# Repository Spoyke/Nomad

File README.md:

# **Son Spatial**
*Projet étudiant S7*

## Description du projet 

Ce projet a pour objectif de créer un système audio immersif mobile grâce à un réseau d’amplificateurs audio, capables de spatialiser le son. Le principe repose sur la distribution et le traitement différencié des signaux audio entre plusieurs amplificateurs, afin de recréer une expérience sonore 3D pour l’utilisateur. Le système s'adapte aux différentes pièces pour trouver 

### Principe de fonctionnement 

#### Microcontrôleur maître

- Reçoit le contenu audio à diffuser (ex : musique, film, jeu vidéo).
- Traite et décompose le signal audio pour chaque ampli, en fonction de leur position relative par rapport à l’utilisateur.
- Envoie les données audio adaptées à chaque ampli via un protocole de communication sans fil.

#### Amplificateurs audio

- Reçoivent les signaux audio spécifiques (ex du stéréo : piste gauche pour l’ampli gauche, piste droite pour l’ampli droit).
- Convertissent le signal numérique en signal analogique, l’amplifient, et le diffusent via des haut-parleurs.
- Synchronisent leur diffusion pour éviter les décalages.

### Exemple

Si un son provient de la gauche dans le contenu audio, l’utilisateur l’entendra principalement depuis l’ampli situé à sa gauche, avec une atténuation progressive vers la droite. Plus le nombre d’amplis est élevé (ex : 4 ou 6), plus la précision de la spatialisation est fine (avant/arrière, haut/bas).

## Architecture du projet

Le projet est divisé en deux parties principales, chacune avec des objectifs techniques spécifiques :

### Partie électronique

Cette partie correspond à la concéption et à la réalisation des amplificateurs audio.

#### Fonctions clés 

- Récupération du signal audio numérique
- Conversion numérique → analogique
- Amplification du signal

### Partie Informatique

Cette partie comporte la programmation des microcontroleurs (esp32), Rasberry PI, application mobile.
On vise à traiter le son et assurer une communication synchrone entre le microcontrôleur maître et les amplis.
- Le traitement de signal sera géré par la Rasberry Pi commandé via une interface mobile. 
- La communication entre l'application du telephone et la raspberry pi se fera via un serveur local WebSocket hebergé par la raspberry.
- La diffusion de la musique entre la raspberry pi et l'esp32 se fera à travers un serveur local Icecast hebergé par la raspberry.

### Partie mécanique

Cette partie vise à conceptionner plusieurs robots capables de se déplacer dans une pièce. 

#### Fonctions clés

- Extraction des pistes (gauche/droite, avant/arrière)
- Synchronisation des amplis

## Compte rendus de séance
### Séance 1 (16/09/2025)

*Julie, Simon, Gabriel* :

Réalisation en amont des schématique :
- Amplificateur audio pour diffuser du son via une application mobile
- Mécanique pour déplacer l'enceinte et éviter les obstacles
  
Mettre en commun les schématique afin de commander les composantes. 

*Axel, Aleksandar* : 

Etablir une communication entre les esp32 - Rasberry Pi - Téléphone
Transmission de son via une application mobile

### Séance 2 (23/09/2025)

"Julie, Simon, Gabriel" : 

- Fin de la réalisation et mise en commun des schémas de l'ampli audio et du robot.
- Ajout d'un capteur à ultrason au robot pour qu'il puisse détecter et anticiper les obstacles. Utilisation du HC-SR04.
- Choix final de l'esp32 et des empreintes des composants pour le PCB. 
- Début de la conception du PCB.

"Axel, Aleks" :

Design de l'interface de l'application
Début de communication entre un esp32 et la raspberry Pi

"Globale" :
- Recherche sur la façon dont les robots se localiser et comment l'implémenter : On utilisera l'intensité du signal émit par la raspberry pi à l'esp32 pour déterminer la distance entre les deux (plus l'intensité est faible, plus la distance est grande)

Planning prévisionnel :

### Séance 3 (30/09/2025)

Simon : commande des composants, continuer le PCB

Gabriel : Finition placement des composants pour le routage, routage des composants sauf pour l'esp32. 

Aleksandar : ecrire un code pour teste l'intensité d'un signal wifi avec un appareil. On remarque que des interférences viennent rapidement perturber le signal. Il faudrait amplifier le signal wifi ou trouver un autre solution pour le localisation des robots.

Axel : transmission d'un fichier audio avec la rasberry Pi sur l'esp32. Vérifier que le signal est bien lu sur l'esp32 avec un oscilloscope. Le son n'est pas assez puissant pour pouvoir l'écouter.Implémentation d'un système d'amplification du courant à la prochaine séance via le dac de l'esp32

Julie: conception mécanique du robot (modélisation Onshape)

### Séance 4 (07/10/2025)

Simon : Recherche sur les moyens de gérer les déplacement des amplis audio et reprérer les amplis dans l'espace. Utilisation de l'intensité du signal pour déterminer la distance entre la raspberry pi et les esp32. Et, les esp32 entre eux, en demendans au esp de transmettre un signal périodiquement pour permettre aux autres de déterminer la distance avec ce dernier. Dans le cas du projet de conférencier, le conférencier porte la raspberry pi et les esp32 se placent dans un rayon de 3m autour de ce dernier. Et, à une certaine distance (à déterminer) entre eux. Ainsi, chaque esp32 va essayer de rester à une distance de 3m du conférencier et suffisament espacé des autres esp32.

 Gabriel : Correction PCB

 Aleks : Correction du code pour l'intensité du signal wifi, manipulation entre deux ESP32 pour vérifier si l'un capte l'autre. On c'est procurer une antenne d'Arès que l'on a mis sur l'ESP32 ce qui a permis de corriger la perturbation des signaux et augmenter leur intensité à la réception de l'ESP32. Vérification de l'intensité du signal émis par un partage de connexion d'iphone en fonction de la distance

 Julie : Conception méca 

 Axel : Lecture du son reçue sur l'esp32 depuis la raspberry avec l'ampli audio LM386. Actuellement le son est de très mauvaise qualitée, mais reconnaisable, car il est diffusé par le DAC de l'esp32. Deux objectifs pour la prochaine séance : - essayer un autre DAC pour voir si la qualité est meilleurs et mise en place de l'application pour commencer le contrôle de la raspberry via le telephone.

### Séance 5 (21/10/2025)

Aleks : Implémentation d'un système de connexion dans le code qui scan les signaux Wi-Fi aux alentours, a présent, il est possible de se connecter a un réseau Wi-Fi tant que l'ESP32 capte le signal et tant que l'on connait le mot de passe du wifi (falcutatif)

Axel : Utilisation du LM386 mais peu fructueuse car il faut mettre un son de très faible amplitude ( ~= 50 mv max à cause du gain de 20 de l'ampli ), qui est presque impossible à avoir avec le DAC 8 bits de l'esp32. Test d'un ampli audio I2S pendant les vacances.

Simon : Début du travaille sur la synchronisation des ESP32 : La raspberry pi envoit des pacquets de données d'une taille à définir en fonction de la qualité du son et de la mémoire disponible sur l'esp32. Dans ce paquet, il y a 3 éléments : l'heure (nombre de microseconde depuis l'epoch) de la rasbperry pi lors de l'envoie du paquet, l'heure où le son doit être joué par l'esp32 et les données du son. De cette façon, la latence peut être estimer la latence qu'il y a eu en comparant l'heure de transmission et l'heure de l'esp32.  

Gabriel : finalisation pcb, creation gerbers, envoi en production

### Séance 6 (4/11/2025)

Aleks : Début de code sur la spatialisation des ESP32, le but sera d'estimer (pour l'instant de manière ni précise et plutôt naïve) la distance entre l'esp32 et la raspberry en fonction de l'intensité RSSI du signal wif.

Axel : Sur mon réseau wifi à domicile, tout est ok niveau transmission de l'audio et synchronisation. Arrivé à l'école, je me rends compte que le réseau de l'ecole bloque certains port d'écoute nécessaire à la partie informatique. Changement du partie du moyen de communication ( Mqtt -> serveur local WebSocket ).

Simon : Mise en place de multithreading pour permettre à l'esp32 de réaliser ses tâches (réception, émission, déplacement et envoit du son à l'ampli audio) en parallèle. Et, travaille sur la synchronisation : mise en place d'une queue pour stocker les paquets reçuent et pas encore traités car la réception des données est plus rapide que le traitement des paquets. Une fois le traitement du paquet terminé, le code créé un timer qui se déclanchera dans (heure du son à jouer - heure raspberry pi).  
 
Gabriel : verification avancement commande pcb, tests de fonctionnement capteur ultrasons, point sur la repartition des tâches avec le reste de l'equipe

Julie : Impression du premier prototypage du boîtier d'ampli audio. Tester l'ultrason et les moteurs pour la prochaine séance. Il faut aussi commander les moteurs, les esp32, les haut parleurs et les batteries pour la prochaine séance. 

### Séance 7 (19/11/2025)

Gabriel : Entretien sur fiche de compétances, recherche composants pour soudure pcb, reflexion à des solutions aux problèmes d'empruntes de composants 

Julie : Soudure des composants

Simon et Aleks : Travail sur la mesure de la distance entre les esp32 pour qu'ils puissent rester à une certaine distance les uns des autres. La première idée, d'utilisé le RSSI comme avec la raspberry pi ne fonctionne pas. La communication n'est pas direct, elle passe par la raspberry pi. Une solution serait d'utiliser ESP-Now pour communiquer directement entre les esp32 mais, cela signifierait de devori couper la communication wifi avec la raspberry pi quelque temps pour émettre un signal capté par les autres esp32.

Axel : Le son est synchronisé avec 3 esp32s, il faut maintenant le spatialiser.

### Séance 8 (25/11/2025)

Axel : Le son est maintenant stéréo. Prochaine étape : enregistrement et diffusion de la voix via un micro I2S

Simon Et Aleks : On a fait fonctionner le capteur à ultrason pour détecter les obstabcles sur la routes des amplis. Et, on a commencé travaillé sur le fonctionnement des moteurs.

Gabriel et Julie : Soudure des composants qui n'avaient pas les bonnes empruntes. Reflexion sur la prochaine version du pcb

### Séance 9 (02/12/2025)

Gabriel : Test du fonctionnement des composants et du fonctionnent général de la carte. applications solutions des problèmes de composants.

Simon : Test du PCB, la diode de schotky protégeant le circuit bloque la tension d'alimentation de 12V. Il y a des étincelles lorsqu'on branche le 12 d'une alim de labo à la carte. Le LDO ne fonctionne pas, il ne sort pas de 5V, le problème peut venir des soudures qui sont moins bonnes à cette endroit. Le LDO transformant le 5V en 3.3V fonctionne mais chauffe beaucoup, il n'y a peut être pas de problème, le drive moteur peut demander beaucoup de courant, ce qui fait chauffer le composant mais, il faudra réfléchir à un moyen de réduire la chaleur du composant dans le prochain PCB. Les Leds indiquant qu'il y a du 12V et du 1.8V ne fonctionnent pas (composant déféctueux ?). On a commencé à câbler la partie amplification avec l'esp32 mais il faut adapter le code pour pouvoir contrôler le composant.  

Axel : Test du micro I2S pas concluant => prochaine solutions : utilisation du micro du telephone

Aleks : Début de recherche et de programmation pour le mouvement des moteurs

Point sur la solution technique du déplacement et la répartition des tâches: 

### Séance 10 (09/12/2025)

Axel : Test du micro I2S enfin concluant, possibilité de le lire sur le pc, il faut maintenant l'envoyer sur le serveur icecast

Gabriel : Répartition des composants sur 3 cartes differentes avec Simon, création projets kicad pour les prochains pcbs, schéma elec carte commande, recherche empruntes et symboles pour composants.

Simon : Travail sur le schéma du PCB de la partie audio, vérification des calculs, du choix et du placments des composants. Tout est bon, le plus gros changement par rapport à la version antérieur est le fait d'utiliser le PWR_MODE1 de l'ampli qui lorsque l'amplification est faible, l'ampli tire son alimentation depuis une source externe plus faible (qui vient du buck) pour moins consommer. Cependant, il faut vérifier que le courant fournit par le buck peut supporter cet ajout et s'il peut le faire sans problème (chauffe etc...). Réflexion sur le déplacment des robots, j'ai trouvé une façon qui même si elle est peu précise devrait suffire pour l'application, sans ajouter de nouveau composant : le robot cherche à se mettre à une certaine distance de la raspberry pi avec le calcul de distance basé sur le RSSI du signal reçu. Et, avec les deux capteurs à ultrasons, le robot cherche à se mettre à une certaine distance des autres robots (les capteurs à ultrasons ayant une porté de 4m). On peut donc faire en sorte que les robots soit à bonne distance de la raspberry pi et les uns des autres pour fournir un son sur une large zone, ce qui est le but du conférencier.  

Aleks : Continuation de la programmation du mouvement des moteurs, mesure et estimation de la distance entre l'esp32 et la raspberry PI avec le RSSI

### Séance 11 (16/12/2025)

Aleks : Estimation de la distance entre esp32 et Raspberry PI faite, code du MotorDriver (TB6612FNG) terminé (en théorie). Objectif de la prochaine séance : codé un encodeur et les moteurs en eux-même.

Simon : Réalisation du PCB de la partie audio qui est presque terminé, mais il faudra attendre la prochaine séance pour envoyer la commande et être sûr qu'il puisse être utilisé avec les autres modules du robot (connecteurs aux bons endroits et dont la connexion entre les autres PCB n'est pas géné par les composants. J'ai aussi fait un bilan du courant consommé par le robot et je me suis rendu compte que le buck ne pourrait pas fournir un courant suffisant lorsque tous les composants fonctionnent au maximum (ce qui devrait être assez rare). On a donc décidé avec Gabriel d'utiliser deux buck (soit le buck actuelle qui sera utilisé jusqu'à ce qu'on le remplace par un autre buck plus puissant à un endroit prévu. Soit on utilise deux fois le même buck mais un des deux serait décdié au fonctionnement de l'ampli.).  

### Séance 12 (13/01/2026)

Tout le monde : Mise en accord sur le planning prévisionnel

Aleks : début de la partie cartographie en expérimentant des capteurs dont le fonctionnement est similaire à un Lidar à l'aide d'une librairie Arduino, pour le moment pas de résultat concret à cause de certaine erreur lié a la partie programmation et au branchement des PINs

Simon : Mise au propre du planning prévisionnel sur Google Agenda (lien tout en bas). Fin du routage de la partie audio.

Gabriel : Finitions schéma elec carte CMD, début routage carte CMD, verification routage partie audio

Axel : Début d'utilisation et de diffusion du son du micro sur un esp32.

Julie : Revoir les capteurs pour mesurer la distance de capture objet
Modifier et finir la schématique pour l'implémenter avec le PCB d'alimentation. Voir avec Gabriel pour le routage. 

### Séance 13 (20/01/2026)

Simon : Fin du routage du PCB de la partie audio. 

Gabriel : Routage PCB Cmd, recherche composants.

Axel : Complication au niveau de la diffusion de la voix, un problème surement lié au format de données envoyée

Julie: Etude des capteurs

Aleks : Fonctionnement du détecteur infrarouge VL53L0X, estimation correcte jusqu'a une distance d'environ 1m.

### Séance 14 (27/01/2026)

Gabriel : fin du routage pcb cmd

Simon : Fin du routage de la partie audio (adaptation du pcb de la partie audio au pcb de la partie commande). J'ai aussi essayé de faire fonctionner le premier PCB (en enlevant le buck qui ne fonctionnait pas) pour faire des tests avec l'ampli audio. Notamment communiquer avec lui et le configurer pour qu'il soit conforme à ce qu'on à besoin (puissance maximale, moyen de communication (I2S), type d'alimentation...). 

Axel : La transmission du micro depuis le telephone vers l'esp32 est fonctionnelle

Julie : Branchement d'un moteur avec le module driver pour faire tourner le moteur. 

Aleks: Finalisation "théorique" du programme concernant la cartographie, mais il faut tester ce dernier.

### Séance 15 (03/02/2026)

Julie : Deuxième prototype de boitier imprimé 3D. A tester avec deux moteurs et mesurer le courant nominal pour un fonctionnement normal. Voir le support le poids avec l'assemblage. 

Simon et Aleks : On a essayé de faire fonctionner l'ampli de l'ancien PCB. Le PCB a différents problème comme le manque de résistance de pull-up sur les pins de l'I2C. Ce qui a compliquer la tâche. Au final, on arrive à envoyer la configuration à l'ampli mais on n'arrive pas à demander des données de l'ampli. 

Gabriel : finalisation du routage cmd + création d'un schéma de cablage pour le test des moteurs. Cablage de ces moteurs et début de création d'un programme de test.

### Séance 16 (10/02/2026)

Simon et Aleks : On a compris pourquoi la communication avec le TAS2780 ne fonctionnait pas : l'ampli utilise du 1.8V pour ses pins numériques alors que l'esp32 utilise du 3.3V. Et en recevant du 3.3V, l'ampli se met en sécurité. Ce qui empêche la communication. 

Gabriel : Continuation du programme de test moteurs, réussite, les moteurs tournent. Tests avec Julie du couple des moteurs alimentés directement sans controleur sur le prototype du robot, et tests de couple sur les moteurs controlés depuis l'esp 32.

Axel : Avancement dans la voix, plus beaucoup de micro coupures dues au rechargement du buffer

Julie : Reprise du PCB Commande, notamment il faut changer les empreintes suite à l'arrivée de la deuxième version du PCB contenant des mauvaise empreintes. 

### Séance 17 (17/02/2026)

Simon et Gabriel : Soudure de la carte 

Julie : Continuation du PCB commande. La commander pour la recevoir à la rentrée. 

### Séance 18 (10/03/2026)

Simon : Soudure des derniers composants sur le pcb audio (connecteur). Et test de la carte : -> la communication I2C fonctionne mais pour l'instant il n'y a pas de son en sortie de l'ampli. 

Gabriel : Création montage pour test encodeurs et début création code test encodeurs.

Julie : Continuation du PCB commande

### Séance 19 (17/03/2026)

Gabriel : Test encodeurs, création morceaux de code pour detecter le sens de rotation du moteur aunsi que valeur absolue pour vérifier vitesse. Finitions pcb fait par Julie.

Julie : Verification PCB et commande du PCB.

Simon : Travail sur le PCB de la partie audio -> L'I2C semble fonctionner

### Séance 20 (24/03/2026)

Gabriel : Finitions code encodeurs, test avec driver moteurs.

Julie : Soudure sur le PCB commandé la semaine précédente. Vérification des erreurs corrigés (empreintes, tailles pistes pour laisser passer le courant). Dimension du boitiers à refaire pour optimiser l'emplacement du PCB, moteurs et haut parleur. 

Simon : Travail sur le PCB de la partie audio, l'I2C semble fonctionner mais je ne sais pas pourquoi. Quand je met l'adresse du composant, la communication ne passe pas mais quand je met une autre adresse (0x38) la communication semble fonctionner sauf quand j'essaye de lire les valeurs d'un registre qui crée des problème. De même quand j'essai de lancer l'ampli, la communication ne fonctionne pas mais quand je n'essai pas de lancer l'ampli et que j'écrit seulement dans les registres de configuration, la communication semble fonctionner. Le problème vient peut être du pin d'adressage du composant mais après l'avoir ressoudé avec Patricia, je n'ai pas vu de différence dans les résultats. L'erreur dans la lecture vient peut-être du code qui ne terminait jamais la transmission mais encore, sans terminer la communication, j'avais des valeurs quand je lisais plusieurs registres différents et dans la même communication.

Axel : Son du micro enfin fonctionnel sur l'ESP32, il faut maintenant harmoniser le code de la gestion de l'audio

### Séance extra 21 (07/04/2026)

Teste de l'alimentation du PCB : 3V3, 5V, 12V marchent très bien. En revanche, le PCB audio fait court-circuiter une piste, ce qui entraine le surchauffe de la bobine. L'esp 32 est fonctionne bien sur le PCB et les connecteurs sont bien reliés aux capteurs. 

## Ressources

### Lien utiles

Diapo : https://docs.google.com/presentation/d/1eaNsvsmn-reTe-8X8-2-HZ8j_HwDIsKxUu0F8LIjo8Q/edit?usp=sharing \
Rapport : https://docs.google.com/document/d/1yTh4eJWGzI2o9GAGtWadODZ8SpGP1pLww7qxfcwqxjY/edit?usp=sharing \
https://www.notion.so/Partie-informatique-266923f17b6e80f486edd3fc771489f0 \
Infos MPU6050 https://docs.google.com/document/d/1O3AgjvM2_tZX7ABNkbS3lNtyRqeFLNvJ6qVK9URJxNs/edit?usp=sharing

### RSE

### Planning prévisionnel du 2nd semestre

https://calendar.google.com/calendar/ical/73473c3522efe55f20496e4b81c19aa0aaffa0a2a7005d1d658da9e635591a50%40group.calendar.google.com/public/basic.ics

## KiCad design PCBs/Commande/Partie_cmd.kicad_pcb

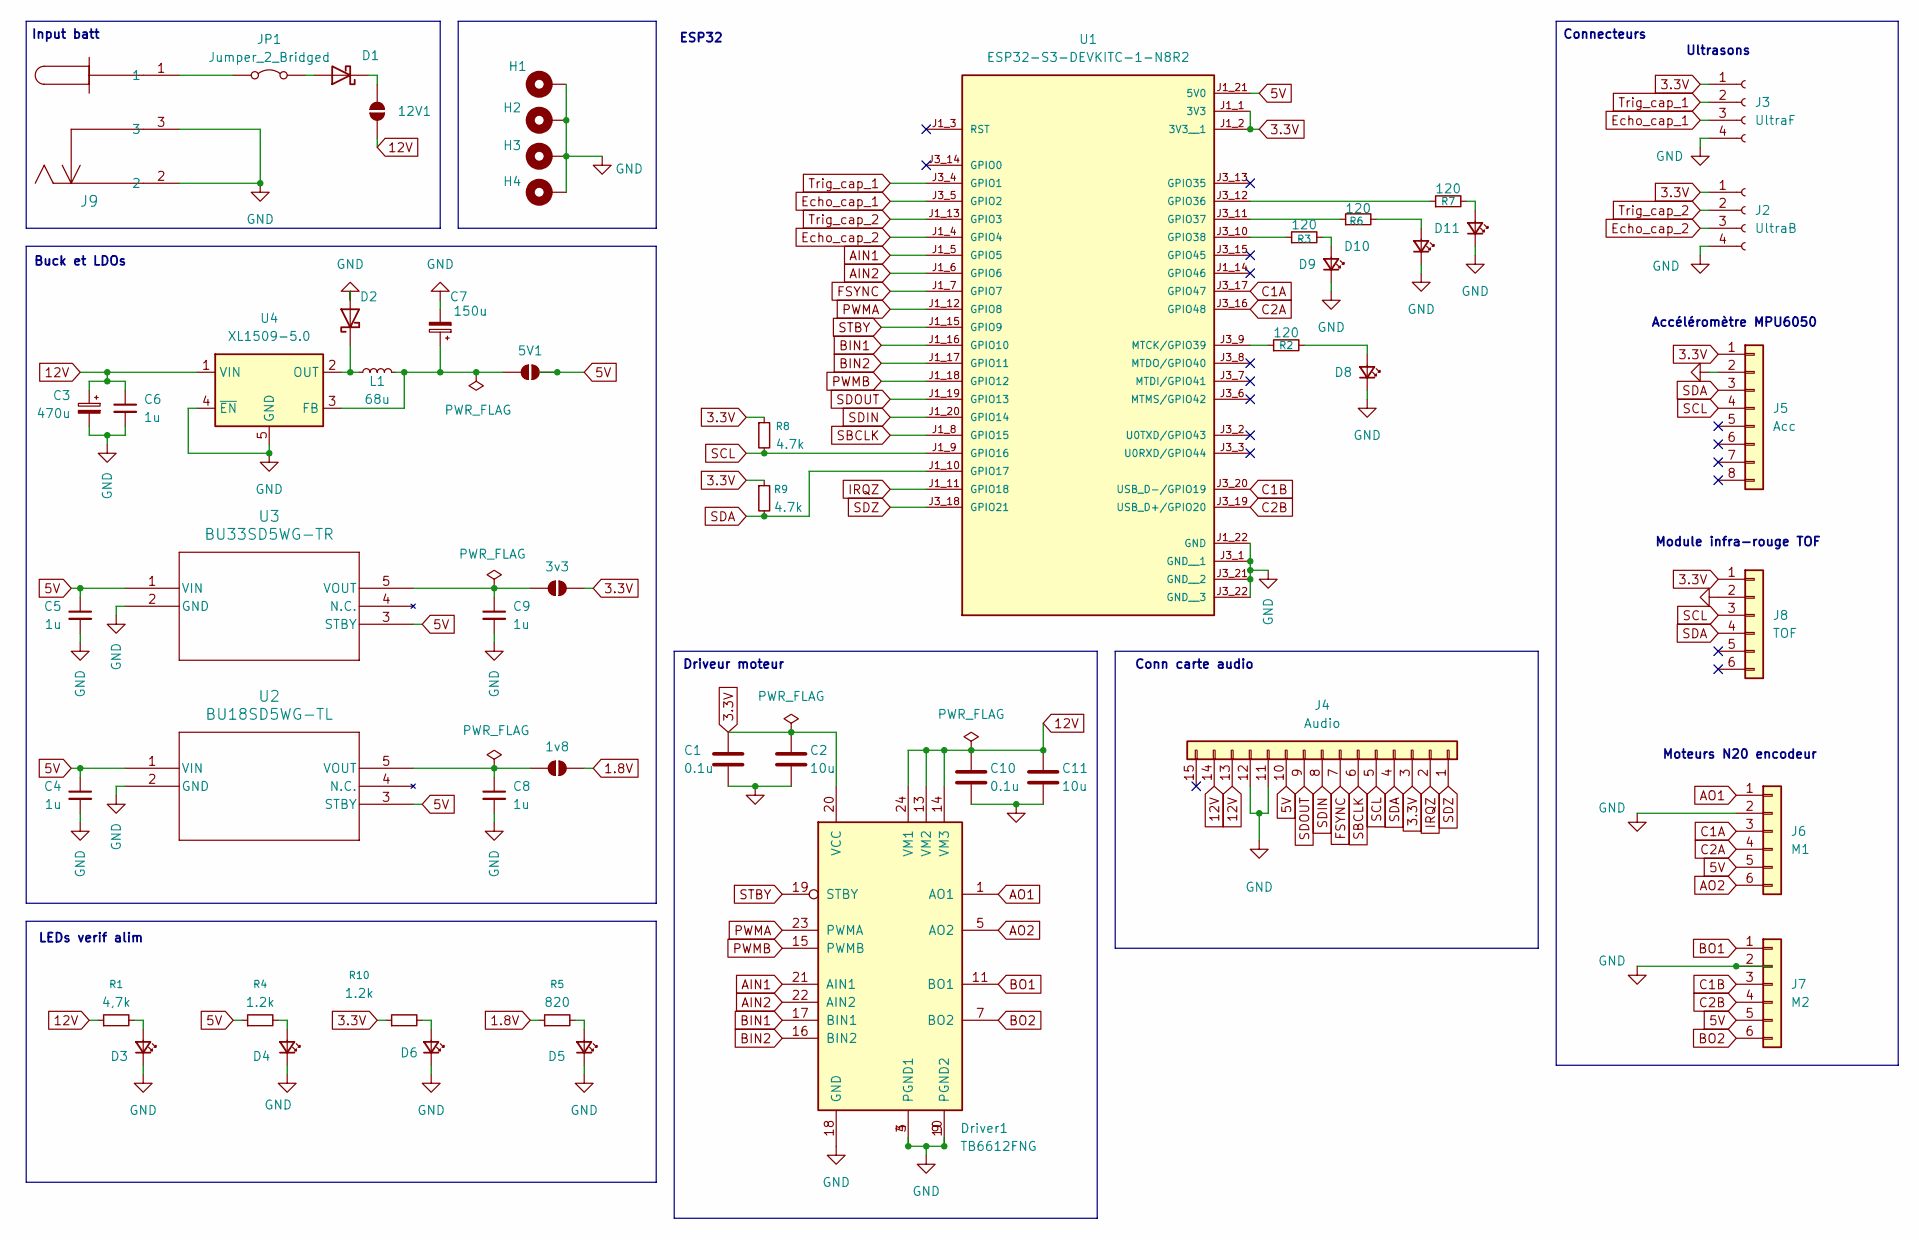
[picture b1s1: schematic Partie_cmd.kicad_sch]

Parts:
1v8, 3v3, 5V1, 12V1: SolderJumper_2_Open; SolderJumper-2_P1.3mm_Open_TrianglePad1.0x1.5mm
C1, C10: 0.1u; C_0402_1005Metric
C2, C11: 10u; C_0805_2012Metric
C3: 470u; CP_Elec_8x10.5
C4, C5, C6, C8, C9: 1u; C_0603_1608Metric_Pad1.08x0.95mm_HandSolder
C7: 150u; CP_Elec_6.3x7.7
D1, D2: MBRS320; D_SMC
D3, D4, D5, D6, D8, D9, D10, D11: LED_Small; LED_0603_1608Metric_Pad1.05x0.95mm_HandSolder
Driver1: TB6612FNG; SSOP-24_5.3x8.2mm_P0.65mm
H1, H2, H3, H4: MountingHole_Pad; MountingHole_2.5mm_Pad_Via
J2: UltraB; PinHeader_1x04_P2.54mm_Vertical
J3: UltraF; PinHeader_1x04_P2.54mm_Vertical
J4: Audio; PinSocket_1x15_P2.00mm_Vertical
J5: Acc; PinHeader_1x08_P2.54mm_Vertical
J6: M1; JST_PH_B6B-PH-K_1x06_P2.00mm_Vertical
J7: M2; JST_PH_B6B-PH-K_1x06_P2.00mm_Vertical
J8: TOF; PinHeader_1x06_P2.54mm_Vertical
J9: 694106105102; CONN3_06105102_WRE
JP1: Jumper_2_Bridged; TestPoint_2Pads_Pitch2.54mm_Drill0.8mm
L1: 68u; L_0805_2012Metric_Pad1.05x1.20mm_HandSolder
R1: 4,7k; R_0603_1608Metric_Pad0.98x0.95mm_HandSolder
R2, R3, R6, R7: 120; R_0603_1608Metric_Pad0.98x0.95mm_HandSolder
R4, R10: 1.2k; R_0603_1608Metric_Pad0.98x0.95mm_HandSolder
R5: 820; R_0603_1608Metric_Pad0.98x0.95mm_HandSolder
R8, R9: 4.7k; R_0603_1608Metric_Pad0.98x0.95mm_HandSolder
U1: ESP32-S3-DEVKITC-1-N8R2; XCVR_ESP32-S3-DEVKITC-1-N8R2; PARTREV V1
U2: BU18SD5WG-TL; SSOP5_ROM-L
U3: BU33SD5WG-TR; SSOP5_ROM-L
U4: XL1509-5.0; SOIC-8_3.9x4.9mm_P1.27mm

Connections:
1.8V: 1v8.2 (B), R5.1
3.3V: 3v3.2 (B), C1.1, C2.1, Driver1.20 (VCC), J2.1, J3.1, J4.3, J5.1, J8.1, R8.1, R9.1, R10.1, U1.J1_1 (3V3), U1.J1_2 (3V3__1)
5V: 5V1.2 (B), C4.1, C5.1, J4.10, J6.5, J7.5, R4.1, U1.J1_21 (5V0), U2.1 (VIN), U2.3 (STBY), U3.1 (VIN), U3.3 (STBY)
12V: 12V1.2 (B), C3.1, C6.1, C10.1, C11.1, Driver1.13 (VM2), Driver1.14 (VM3), Driver1.24 (VM1), J4.13, J4.14, R1.1, U4.1 (VIN)
AIN1: Driver1.21 (AIN1), U1.J1_5 (GPIO5)
AIN2: Driver1.22 (AIN2), U1.J1_6 (GPIO6)
AO1: Driver1.1 (AO1), Driver1.2 (AO1), J6.1
AO2: Driver1.5 (AO2), Driver1.6 (AO2), J6.6
BIN1: Driver1.17 (BIN1), U1.J1_16 (GPIO10)
BIN2: Driver1.16 (BIN2), U1.J1_17 (GPIO11)
BO1: Driver1.11 (BO1), Driver1.12 (BO1), J7.1
BO2: Driver1.7 (BO2), Driver1.8 (BO2), J7.6
C1A: J6.3, U1.J3_17 (GPIO47)
C1B: J7.3, U1.J3_20 (USB_D-/GPIO19)
C2A: J6.4, U1.J3_16 (GPIO48)
C2B: J7.4, U1.J3_19 (USB_D+/GPIO20)
Echo_cap_1: J3.3, U1.J3_5 (GPIO2)
Echo_cap_2: J2.3, U1.J1_4 (GPIO4)
FSYNC: J4.7, U1.J1_7 (GPIO7)
GND: C1.2, C2.2, C3.2, C4.2, C5.2, C6.2, C7.2, C8.2, C9.2, C10.2, C11.2, D2.2 (A), D3.1 (K), D4.1 (K), D5.1 (K), D6.1 (K), D8.1 (K), D9.1 (K), D10.1 (K), D11.1 (K), Driver1.3 (PGND1), Driver1.4 (PGND1), Driver1.9 (PGND2), Driver1.10 (PGND2), Driver1.18 (GND), H1.1, H2.1, H3.1, H4.1, J2.4, J3.4, J4.11, J4.12, J5.2, J6.2, J7.2, J8.2, J9.2, J9.3, U1.J1_22 (GND), U1.J3_1 (GND__1), U1.J3_21 (GND__2), U1.J3_22 (GND__3), U2.2 (GND), U3.2 (GND), U4.4 (~EN), U4.5 (GND), U4.6 (GND), U4.7 (GND), U4.8 (GND)
IRQZ: J4.2, U1.J1_11 (GPIO18)
unnamed: 1v8.1 (A), C8.1, U2.5 (VOUT)
unnamed: 3v3.1 (A), C9.1, U3.5 (VOUT)
unnamed: 5V1.1 (A), C7.1, L1.2, U4.3 (FB)
unnamed: 12V1.1 (A), D1.1 (K)
unnamed: D1.2 (A), JP1.2 (B)
unnamed: D2.1 (K), L1.1, U4.2 (OUT)
unnamed: D3.2 (A), R1.2
unnamed: D4.2 (A), R4.2
unnamed: D5.2 (A), R5.2
unnamed: D6.2 (A), R10.2
unnamed: D8.2 (A), R2.2
unnamed: D9.2 (A), R3.2
unnamed: D10.2 (A), R6.2
unnamed: D11.2 (A), R7.2
unnamed: J9.1, JP1.1 (A)
unnamed: R7.1, U1.J3_12 (GPIO36)
unnamed: R6.1, U1.J3_11 (GPIO37)
unnamed: R3.1, U1.J3_10 (GPIO38)
unnamed: R2.1, U1.J3_9 (MTCK/GPIO39)
PWMA: Driver1.23 (PWMA), U1.J1_12 (GPIO8)
PWMB: Driver1.15 (PWMB), U1.J1_18 (GPIO12)
SBCLK: J4.6, U1.J1_8 (GPIO15)
SCL: J4.5, J5.4, J8.3, R8.2, U1.J1_9 (GPIO16)
SDA: J4.4, J5.3, J8.4, R9.2, U1.J1_10 (GPIO17)
SDIN: J4.8, U1.J1_20 (GPIO14)
SDOUT: J4.9, U1.J1_19 (GPIO13)
SDZ: J4.1, U1.J3_18 (GPIO21)
STBY: Driver1.19 (STBY), U1.J1_15 (GPIO9)
Trig_cap_1: J3.2, U1.J3_4 (GPIO1)
Trig_cap_2: J2.2, U1.J1_13 (GPIO3)

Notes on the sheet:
Buck et LDOs
LEDs verif alim
Input batt
Accéléromètre MPU6050
Moteurs N20 encodeur
Module infra-rouge TOF
Ultrasons
ESP32
Connecteurs
Conn carte audio
Driveur moteur

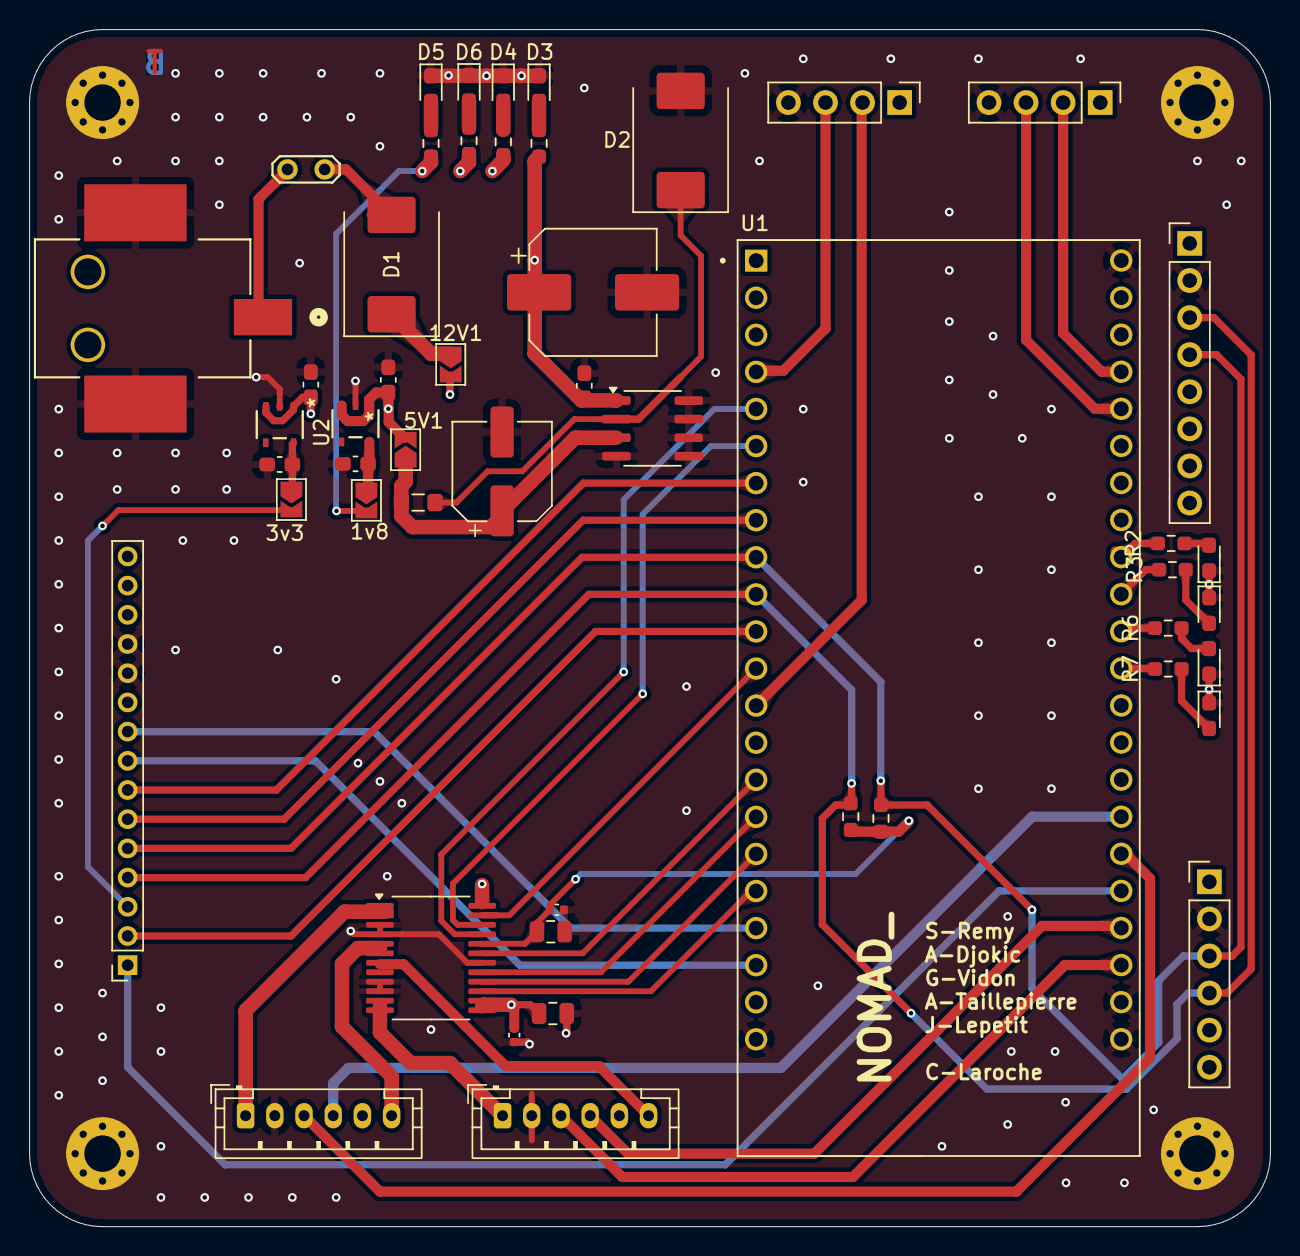
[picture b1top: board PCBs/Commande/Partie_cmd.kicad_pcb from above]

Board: 4 copper layers, 85.0 x 82.0 mm, 54 parts (0 on the bottom side), 51 nets.

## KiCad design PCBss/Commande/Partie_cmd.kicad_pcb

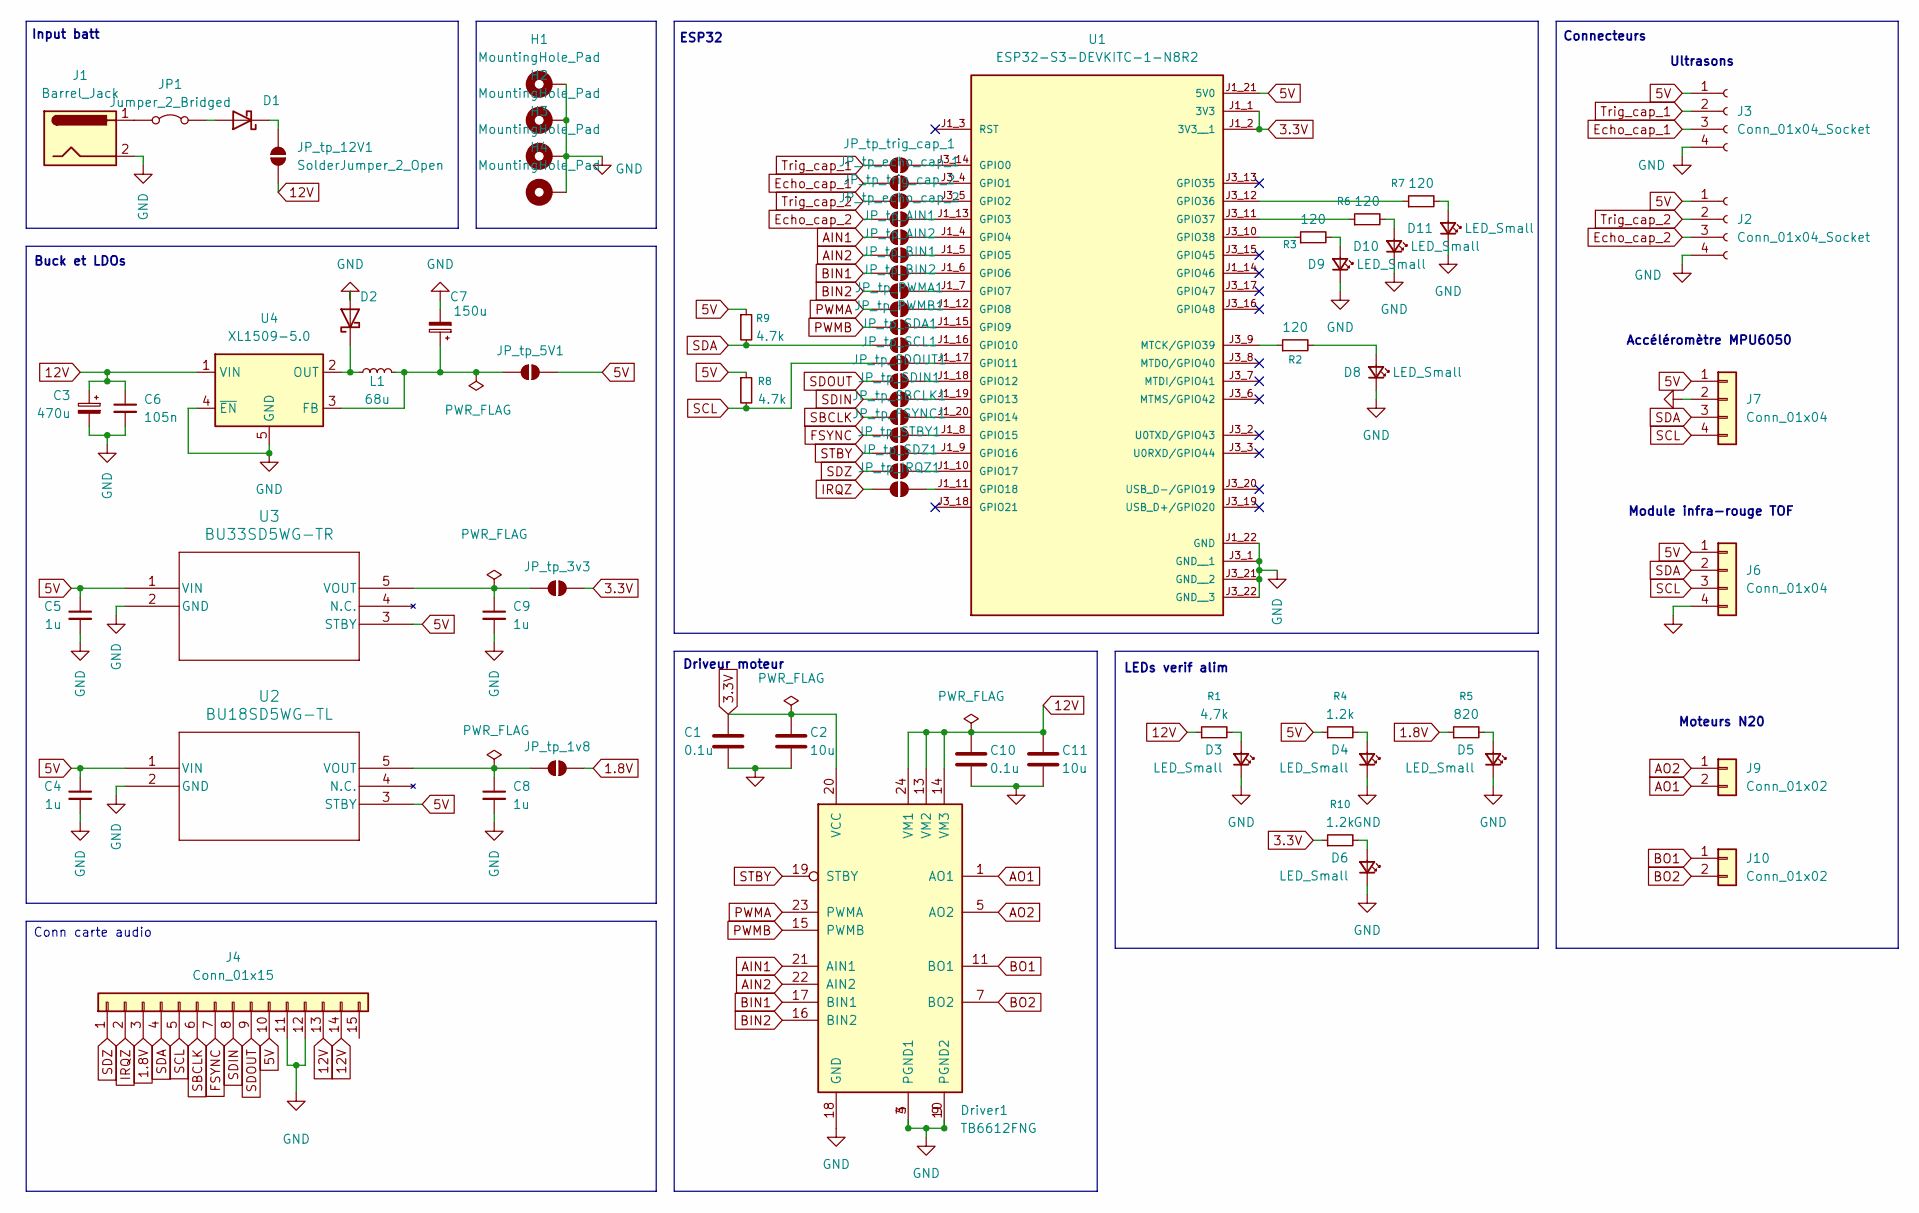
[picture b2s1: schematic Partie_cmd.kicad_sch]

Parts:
C1, C10: 0.1u; C_0402_1005Metric
C2, C11: 10u; C_0805_2012Metric
C3: 470u; CP_Elec_8x10.5
C4, C5, C8, C9: 1u; C_0603_1608Metric_Pad1.08x0.95mm_HandSolder
C6: 105n; C_0603_1608Metric_Pad1.08x0.95mm_HandSolder
C7: 150u; CP_Elec_6.3x7.7
D1, D2: MBRS320; D_SMC
D3, D4, D5, D6, D8, D9, D10, D11: LED_Small; LED_0603_1608Metric_Pad1.05x0.95mm_HandSolder
Driver1: TB6612FNG; SSOP-24_5.3x8.2mm_P0.65mm
H1, H2, H3, H4: MountingHole_Pad; MountingHole_2.5mm_Pad_Via
J1: Barrel_Jack; BarrelJack_Wuerth_694108106102_2.5x5.5mm
J2, J3: Conn_01x04_Socket; PinHeader_1x04_P2.00mm_Vertical
J4: Conn_01x15; PinSocket_1x15_P2.00mm_Vertical
J6: Conn_01x04; PinSocket_1x04_P2.00mm_Vertical
J7: Conn_01x04; PinHeader_1x04_P2.00mm_Vertical
J9, J10: Conn_01x02; JST_XH_B2B-XH-A_1x02_P2.50mm_Vertical
JP1: Jumper_2_Bridged; TestPoint_2Pads_Pitch2.54mm_Drill0.8mm
JP_tp_1v8, JP_tp_3v3, JP_tp_5V1, JP_tp_12V1: SolderJumper_2_Open; SolderJumper-2_P1.3mm_Open_TrianglePad1.0x1.5mm
JP_tp_AIN1, JP_tp_AIN2: SolderJumper_2_Open; SolderJumper-2_P1.3mm_Open_TrianglePad1.0x1.5mm
JP_tp_BIN1, JP_tp_BIN2: SolderJumper_2_Open; SolderJumper-2_P1.3mm_Open_TrianglePad1.0x1.5mm
JP_tp_FSYNC1: SolderJumper_2_Open; SolderJumper-2_P1.3mm_Open_TrianglePad1.0x1.5mm
JP_tp_IRQZ1: SolderJumper_2_Open; SolderJumper-2_P1.3mm_Open_TrianglePad1.0x1.5mm
JP_tp_PWMA1: SolderJumper_2_Open; SolderJumper-2_P1.3mm_Open_TrianglePad1.0x1.5mm
JP_tp_PWMB1: SolderJumper_2_Open; SolderJumper-2_P1.3mm_Open_TrianglePad1.0x1.5mm
JP_tp_SBCLK1: SolderJumper_2_Open; SolderJumper-2_P1.3mm_Open_TrianglePad1.0x1.5mm
JP_tp_SCL1: SolderJumper_2_Open; SolderJumper-2_P1.3mm_Open_TrianglePad1.0x1.5mm
JP_tp_SDA1: SolderJumper_2_Open; SolderJumper-2_P1.3mm_Open_TrianglePad1.0x1.5mm
JP_tp_SDIN1: SolderJumper_2_Open; SolderJumper-2_P1.3mm_Open_TrianglePad1.0x1.5mm
JP_tp_SDOUT1: SolderJumper_2_Open; SolderJumper-2_P1.3mm_Open_TrianglePad1.0x1.5mm
JP_tp_SDZ1: SolderJumper_2_Open; SolderJumper-2_P1.3mm_Open_TrianglePad1.0x1.5mm
JP_tp_STBY1: SolderJumper_2_Open; SolderJumper-2_P1.3mm_Open_TrianglePad1.0x1.5mm
JP_tp_echo_cap_1, JP_tp_echo_cap_2: SolderJumper_2_Open; SolderJumper-2_P1.3mm_Open_TrianglePad1.0x1.5mm
JP_tp_trig_cap_1, JP_tp_trig_cap_2: SolderJumper_2_Open; SolderJumper-2_P1.3mm_Open_TrianglePad1.0x1.5mm
L1: 68u; L_0805_2012Metric_Pad1.05x1.20mm_HandSolder
R1: 4,7k; R_0603_1608Metric_Pad0.98x0.95mm_HandSolder
R2, R3, R6, R7: 120; R_0603_1608Metric_Pad0.98x0.95mm_HandSolder
R4, R10: 1.2k; R_0603_1608Metric_Pad0.98x0.95mm_HandSolder
R5: 820; R_0603_1608Metric_Pad0.98x0.95mm_HandSolder
R8, R9: 4.7k; R_0603_1608Metric_Pad0.98x0.95mm_HandSolder
U1: ESP32-S3-DEVKITC-1-N8R2; XCVR_ESP32-S3-DEVKITC-1-N8R2; PARTREV V1
U2: BU18SD5WG-TL; SSOP5_ROM-L
U3: BU33SD5WG-TR; SSOP5_ROM-L
U4: XL1509-5.0; SOIC-8_3.9x4.9mm_P1.27mm

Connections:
1.8V: J4.3, JP_tp_1v8.2 (B), R5.1
3.3V: C1.1, C2.1, Driver1.20 (VCC), JP_tp_3v3.2 (B), R10.1, U1.J1_1 (3V3), U1.J1_2 (3V3__1)
5V: C4.1, C5.1, J2.1, J3.1, J4.10, J6.1, J7.1, JP_tp_5V1.2 (B), R4.1, R8.1, R9.1, U1.J1_21 (5V0), U2.1 (VIN), U2.3 (STBY), U3.1 (VIN), U3.3 (STBY)
12V: C3.1, C6.1, C10.1, C11.1, Driver1.13 (VM2), Driver1.14 (VM3), Driver1.24 (VM1), J4.13, J4.14, JP_tp_12V1.2 (B), R1.1, U4.1 (VIN)
AIN1: Driver1.21 (AIN1), JP_tp_AIN1.1 (A)
AIN2: Driver1.22 (AIN2), JP_tp_AIN2.1 (A)
AO1: Driver1.1 (AO1), Driver1.2 (AO1), J9.2
AO2: Driver1.5 (AO2), Driver1.6 (AO2), J9.1
BIN1: Driver1.17 (BIN1), JP_tp_BIN1.1 (A)
BIN2: Driver1.16 (BIN2), JP_tp_BIN2.1 (A)
BO1: Driver1.11 (BO1), Driver1.12 (BO1), J10.1
BO2: Driver1.7 (BO2), Driver1.8 (BO2), J10.2
Echo_cap_1: J3.3, JP_tp_echo_cap_1.1 (A)
Echo_cap_2: J2.3, JP_tp_echo_cap_2.1 (A)
FSYNC: J4.7, JP_tp_FSYNC1.1 (A)
GND: C1.2, C2.2, C3.2, C4.2, C5.2, C6.2, C7.2, C8.2, C9.2, C10.2, C11.2, D2.2 (A), D3.1 (K), D4.1 (K), D5.1 (K), D6.1 (K), D8.1 (K), D9.1 (K), D10.1 (K), D11.1 (K), Driver1.3 (PGND1), Driver1.4 (PGND1), Driver1.9 (PGND2), Driver1.10 (PGND2), Driver1.18 (GND), H1.1, H2.1, H3.1, H4.1, J1.2, J2.4, J3.4, J4.11, J4.12, J6.4, J7.2, U1.J1_22 (GND), U1.J3_1 (GND__1), U1.J3_21 (GND__2), U1.J3_22 (GND__3), U2.2 (GND), U3.2 (GND), U4.4 (~EN), U4.5 (GND), U4.6 (GND), U4.7 (GND), U4.8 (GND)
IRQZ: J4.2, JP_tp_IRQZ1.1 (A)
unnamed: D1.2 (A), JP1.2 (B)
unnamed: D1.1 (K), JP_tp_12V1.1 (A)
unnamed: D2.1 (K), L1.1, U4.2 (OUT)
unnamed: D3.2 (A), R1.2
unnamed: D4.2 (A), R4.2
unnamed: D5.2 (A), R5.2
unnamed: D6.2 (A), R10.2
unnamed: D8.2 (A), R2.2
unnamed: D9.2 (A), R3.2
unnamed: D10.2 (A), R6.2
unnamed: D11.2 (A), R7.2
unnamed: J1.1, JP1.1 (A)
unnamed: C8.1, JP_tp_1v8.1 (A), U2.5 (VOUT)
unnamed: C9.1, JP_tp_3v3.1 (A), U3.5 (VOUT)
unnamed: C7.1, JP_tp_5V1.1 (A), L1.2, U4.3 (FB)
unnamed: JP_tp_AIN1.2 (B), U1.J1_4 (GPIO4)
unnamed: JP_tp_AIN2.2 (B), U1.J1_5 (GPIO5)
unnamed: JP_tp_BIN1.2 (B), U1.J1_6 (GPIO6)
unnamed: JP_tp_BIN2.2 (B), U1.J1_7 (GPIO7)
unnamed: JP_tp_FSYNC1.2 (B), U1.J1_8 (GPIO15)
unnamed: JP_tp_IRQZ1.2 (B), U1.J1_11 (GPIO18)
unnamed: JP_tp_PWMA1.2 (B), U1.J1_12 (GPIO8)
unnamed: JP_tp_PWMB1.2 (B), U1.J1_15 (GPIO9)
unnamed: JP_tp_SBCLK1.2 (B), U1.J1_20 (GPIO14)
unnamed: JP_tp_SCL1.2 (B), U1.J1_17 (GPIO11)
unnamed: JP_tp_SDA1.2 (B), U1.J1_16 (GPIO10)
unnamed: JP_tp_SDIN1.2 (B), U1.J1_19 (GPIO13)
unnamed: JP_tp_SDOUT1.2 (B), U1.J1_18 (GPIO12)
unnamed: JP_tp_SDZ1.2 (B), U1.J1_10 (GPIO17)
unnamed: JP_tp_STBY1.2 (B), U1.J1_9 (GPIO16)
unnamed: JP_tp_echo_cap_1.2 (B), U1.J3_4 (GPIO1)
unnamed: JP_tp_echo_cap_2.2 (B), U1.J1_13 (GPIO3)
unnamed: JP_tp_trig_cap_1.2 (B), U1.J3_14 (GPIO0)
unnamed: JP_tp_trig_cap_2.2 (B), U1.J3_5 (GPIO2)
unnamed: R7.1, U1.J3_12 (GPIO36)
unnamed: R6.1, U1.J3_11 (GPIO37)
unnamed: R3.1, U1.J3_10 (GPIO38)
unnamed: R2.1, U1.J3_9 (MTCK/GPIO39)
PWMA: Driver1.23 (PWMA), JP_tp_PWMA1.1 (A)
PWMB: Driver1.15 (PWMB), JP_tp_PWMB1.1 (A)
SBCLK: J4.6, JP_tp_SBCLK1.1 (A)
SCL: J4.5, J6.3, J7.4, JP_tp_SCL1.1 (A), R8.2
SDA: J4.4, J6.2, J7.3, JP_tp_SDA1.1 (A), R9.2
SDIN: J4.8, JP_tp_SDIN1.1 (A)
SDOUT: J4.9, JP_tp_SDOUT1.1 (A)
SDZ: J4.1, JP_tp_SDZ1.1 (A)
STBY: Driver1.19 (STBY), JP_tp_STBY1.1 (A)
Trig_cap_1: J3.2, JP_tp_trig_cap_1.1 (A)
Trig_cap_2: J2.2, JP_tp_trig_cap_2.1 (A)

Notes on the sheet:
Buck et LDOs
LEDs verif alim
Input batt
Accéléromètre MPU6050
Moteurs N20
Module infra-rouge TOF
Ultrasons
ESP32
Connecteurs
Conn carte audio
Driveur moteur

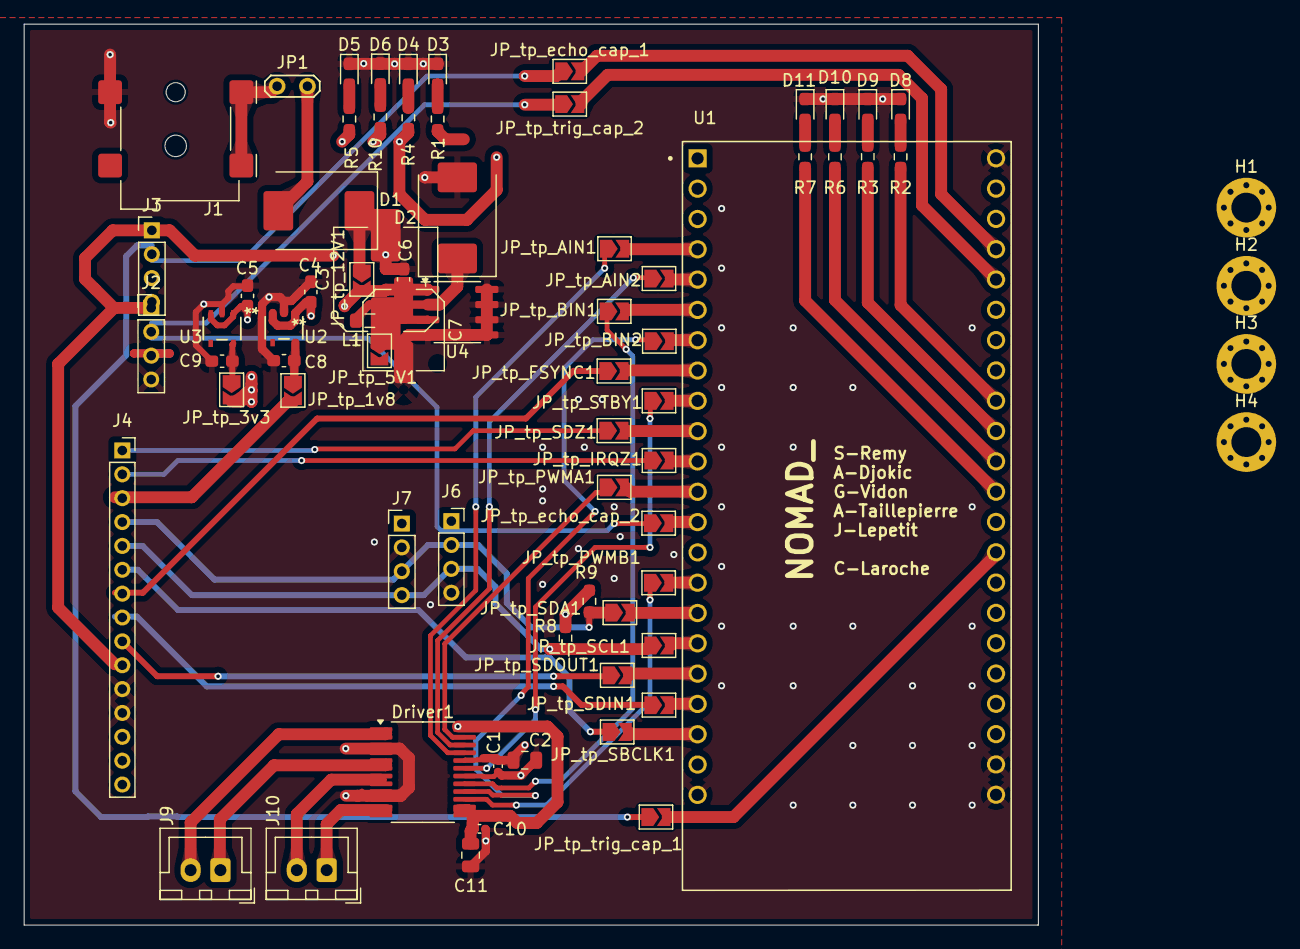
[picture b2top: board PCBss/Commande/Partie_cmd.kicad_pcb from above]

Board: 4 copper layers, 85.0 x 75.5 mm, 73 parts (0 on the bottom side), 66 nets.

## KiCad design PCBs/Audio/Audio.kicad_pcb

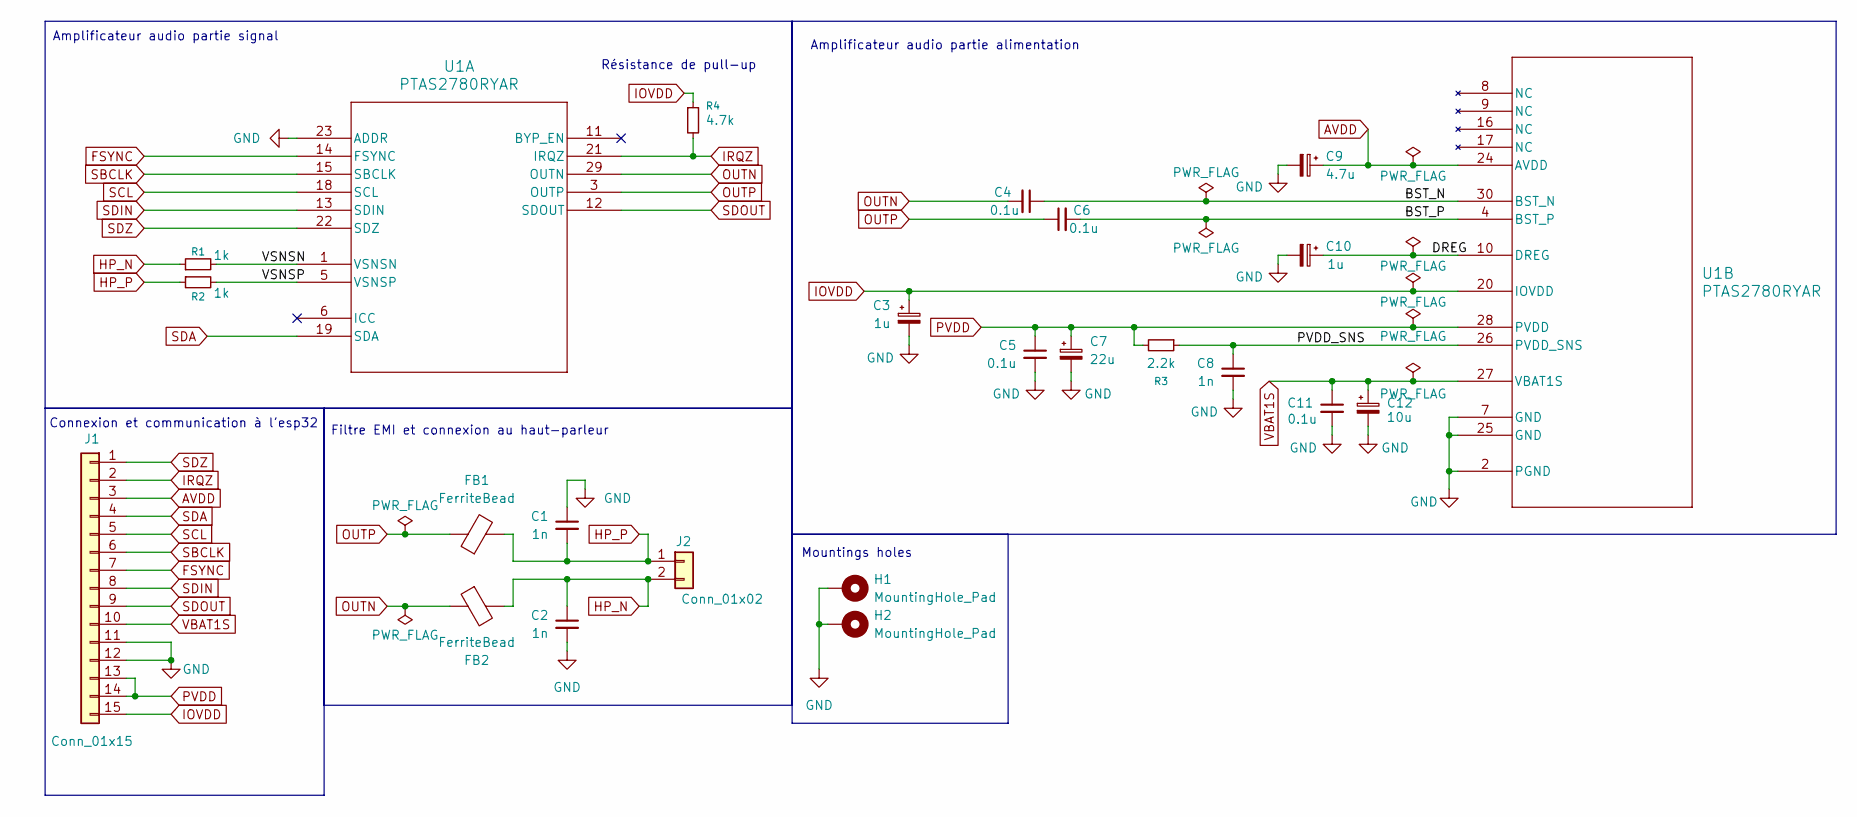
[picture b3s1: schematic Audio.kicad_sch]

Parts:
C1, C2, C8: 1n; C_0603_1608Metric_Pad1.08x0.95mm_HandSolder
C3, C10: 1u; C_0603_1608Metric_Pad1.08x0.95mm_HandSolder
C4, C6, C11: 0.1u; C_0603_1608Metric_Pad1.08x0.95mm_HandSolder
C5: 0.1u; C_0805_2012Metric_Pad1.18x1.45mm_HandSolder
C7: 22u; C_1210_3225Metric_Pad1.33x2.70mm_HandSolder
C9: 4.7u; C_0603_1608Metric_Pad1.08x0.95mm_HandSolder
C12: 10u; C_0805_2012Metric_Pad1.18x1.45mm_HandSolder
FB1, FB2: FerriteBead; C_0805_2012Metric_Pad1.18x1.45mm_HandSolder
H1, H2: MountingHole_Pad; MountingHole_2.2mm_M2_DIN965_Pad
J1: Conn_01x15; PinHeader_1x15_P2.00mm_Vertical
J2: Conn_01x02; PinHeader_1x02_P2.00mm_Vertical
R1, R2: 1k; R_0603_1608Metric_Pad0.98x0.95mm_HandSolder
R3: 2.2k; R_0603_1608Metric_Pad0.98x0.95mm_HandSolder
R4: 4.7k; R_0603_1608Metric_Pad0.98x0.95mm_HandSolder
U1: PTAS2780RYAR; VQFN-HR_RYA_TEX

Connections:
/BST_N: C4.1, U1.30 (BST_N)
/BST_P: C6.2, U1.4 (BST_P)
/DREG: C10.1, U1.10 (DREG)
/PVDD_SNS: C8.1, R3.1, U1.26 (PVDD_SNS)
/VSNSN: R1.2, U1.1 (VSNSN)
/VSNSP: R2.2, U1.5 (VSNSP)
AVDD: C9.1, J1.3, U1.24 (AVDD)
FSYNC: J1.7, U1.14 (FSYNC)
GND: C1.1, C2.2, C3.2, C5.2, C7.2, C8.2, C9.2, C10.2, C11.2, C12.2, H1.1, H2.1, J1.11, J1.12, U1.2 (PGND), U1.7 (GND), U1.23 (ADDR), U1.25 (GND)
HP_N: C2.1, FB2.2, J2.2, R1.1
HP_P: C1.2, FB1.2, J2.1, R2.1
IOVDD: C3.1, J1.15, R4.1, U1.20 (IOVDD)
IRQZ: J1.2, R4.2, U1.21 (IRQZ)
OUTN: C4.2, FB2.1, U1.29 (OUTN)
OUTP: C6.1, FB1.1, U1.3 (OUTP)
PVDD: C5.1, C7.1, J1.13, J1.14, R3.2, U1.28 (PVDD)
SBCLK: J1.6, U1.15 (SBCLK)
SCL: J1.5, U1.18 (SCL)
SDA: J1.4, U1.19 (SDA)
SDIN: J1.8, U1.13 (SDIN)
SDOUT: J1.9, U1.12 (SDOUT)
SDZ: J1.1, U1.22 (SDZ)
VBAT1S: C11.1, C12.1, J1.10, U1.27 (VBAT1S)

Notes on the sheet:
Amplificateur audio partie alimentation
Connexion et communication à l'esp32
Résistance de pull-up
Mountings holes
Amplificateur audio partie signal
Filtre EMI et connexion au haut-parleur

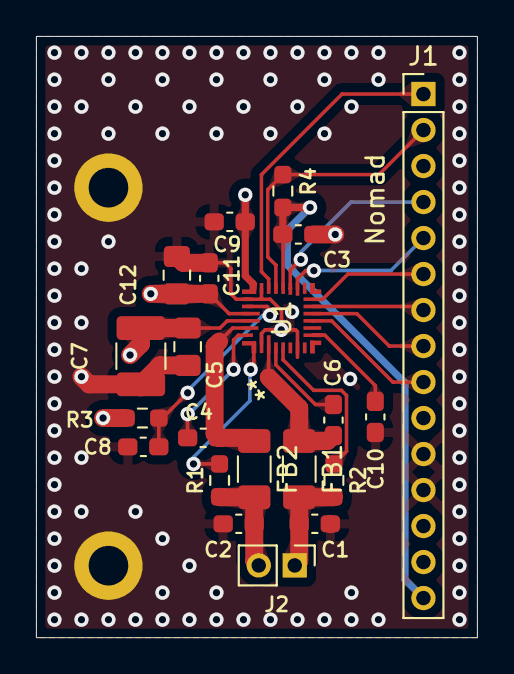
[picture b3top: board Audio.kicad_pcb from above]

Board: 4 copper layers, 24.5 x 33.4 mm, 23 parts (0 on the bottom side), 23 nets.
